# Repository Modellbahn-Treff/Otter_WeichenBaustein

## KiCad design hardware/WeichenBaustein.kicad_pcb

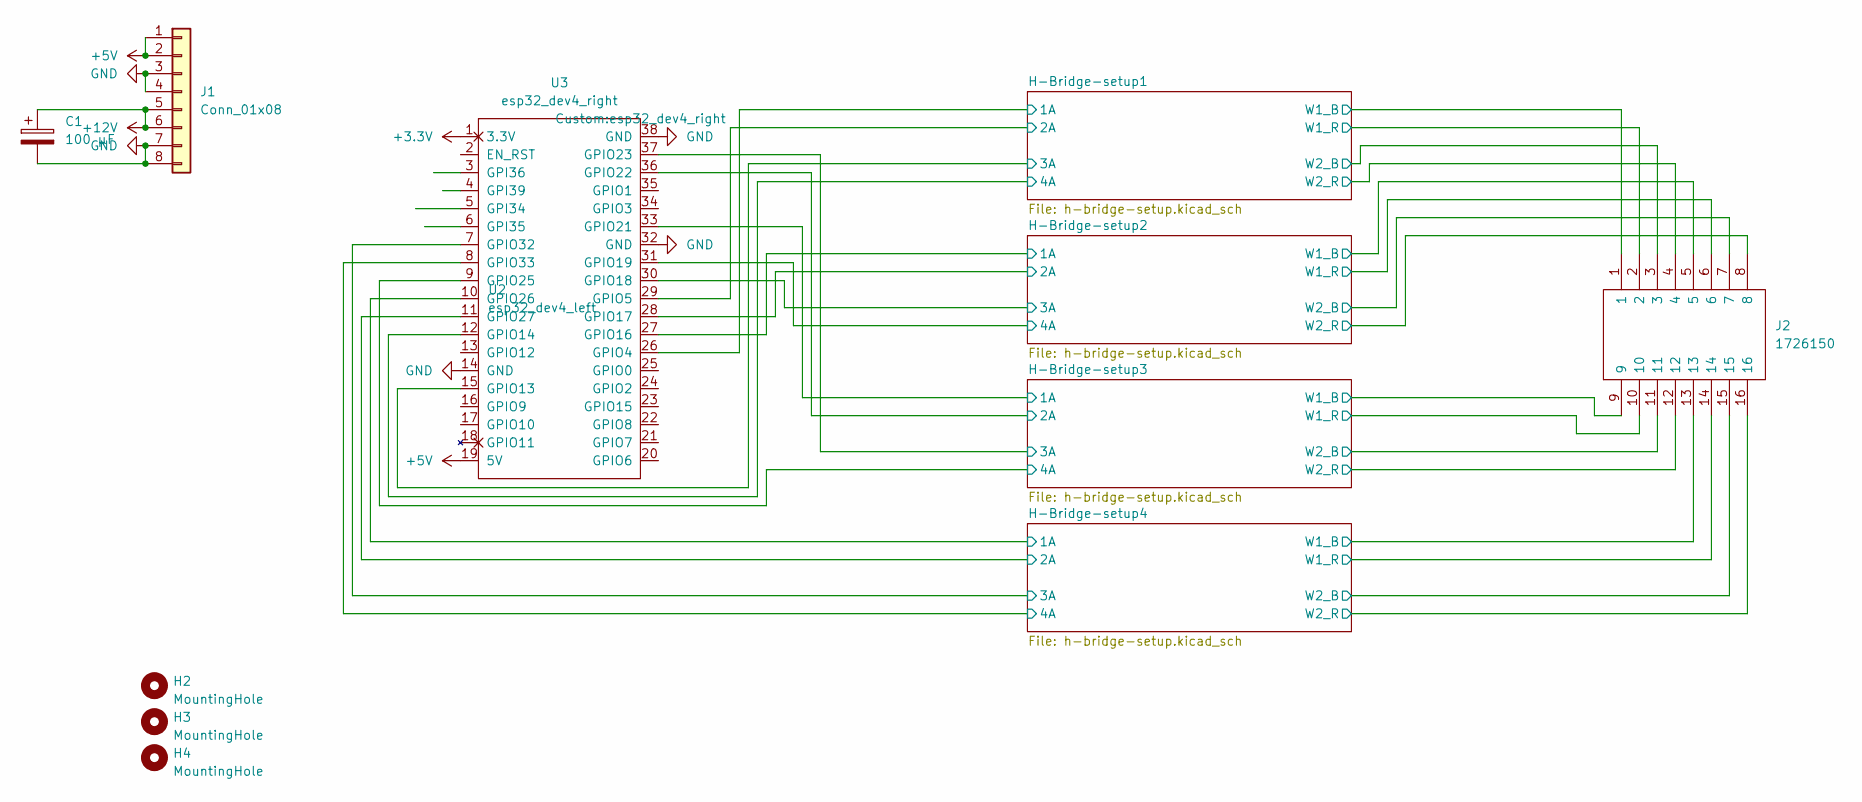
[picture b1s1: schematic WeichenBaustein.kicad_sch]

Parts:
C1: 100 µF; CP_Radial_D6.3mm_P2.50mm
H2, H3, H4: MountingHole; MountingHole_4.3mm_M4
J1: Conn_01x08; 1729186
J2: 1726150; Manufacturer_Part_Number 1726150; Mouser Part Number 651-1726150
U2: esp32_dev4_left; esp32_dev_left
U3: esp32_dev4_right

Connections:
+3.3V: U2.1 (3.3V)
+5V: J1.1, J1.2, U2.19 (5V); also elsewhere on the board
+12V: C1.1, J1.5, J1.6; also elsewhere on the board
/H-Bridge-setup1/1A: U3.26 (GPIO4); also elsewhere on the board
/H-Bridge-setup1/2A: U3.29 (GPIO5); also elsewhere on the board
/H-Bridge-setup1/3A: U2.15 (GPIO13); also elsewhere on the board
/H-Bridge-setup1/4A: U2.12 (GPIO14); also elsewhere on the board
/H-Bridge-setup1/W1_B: J2.1; also elsewhere on the board
/H-Bridge-setup1/W1_R: J2.2; also elsewhere on the board
/H-Bridge-setup1/W2_B: J2.3; also elsewhere on the board
/H-Bridge-setup1/W2_R: J2.4; also elsewhere on the board
/H-Bridge-setup2/1A: U3.27 (GPIO16); also elsewhere on the board
/H-Bridge-setup2/2A: U3.28 (GPIO17); also elsewhere on the board
/H-Bridge-setup2/3A: U3.30 (GPIO18); also elsewhere on the board
/H-Bridge-setup2/4A: U3.31 (GPIO19); also elsewhere on the board
/H-Bridge-setup2/W1_B: J2.5; also elsewhere on the board
/H-Bridge-setup2/W1_R: J2.6; also elsewhere on the board
/H-Bridge-setup2/W2_B: J2.7; also elsewhere on the board
/H-Bridge-setup2/W2_R: J2.8; also elsewhere on the board
/H-Bridge-setup3/1A: U3.33 (GPIO21); also elsewhere on the board
/H-Bridge-setup3/2A: U3.36 (GPIO22); also elsewhere on the board
/H-Bridge-setup3/3A: U3.37 (GPIO23); also elsewhere on the board
/H-Bridge-setup3/4A: U2.9 (GPIO25); also elsewhere on the board
/H-Bridge-setup3/W1_B: J2.9; also elsewhere on the board
/H-Bridge-setup3/W1_R: J2.10; also elsewhere on the board
/H-Bridge-setup3/W2_B: J2.11; also elsewhere on the board
/H-Bridge-setup3/W2_R: J2.12; also elsewhere on the board
/H-Bridge-setup4/1A: U2.10 (GPIO26); also elsewhere on the board
/H-Bridge-setup4/2A: U2.11 (GPIO27); also elsewhere on the board
/H-Bridge-setup4/3A: U2.7 (GPIO32); also elsewhere on the board
/H-Bridge-setup4/4A: U2.8 (GPIO33); also elsewhere on the board
/H-Bridge-setup4/W1_B: J2.13; also elsewhere on the board
/H-Bridge-setup4/W1_R: J2.14; also elsewhere on the board
/H-Bridge-setup4/W2_B: J2.15; also elsewhere on the board
/H-Bridge-setup4/W2_R: J2.16; also elsewhere on the board
GND: C1.2, J1.3, J1.4, J1.7, J1.8, U2.14 (GND), U3.32 (GND), U3.38 (GND); also elsewhere on the board

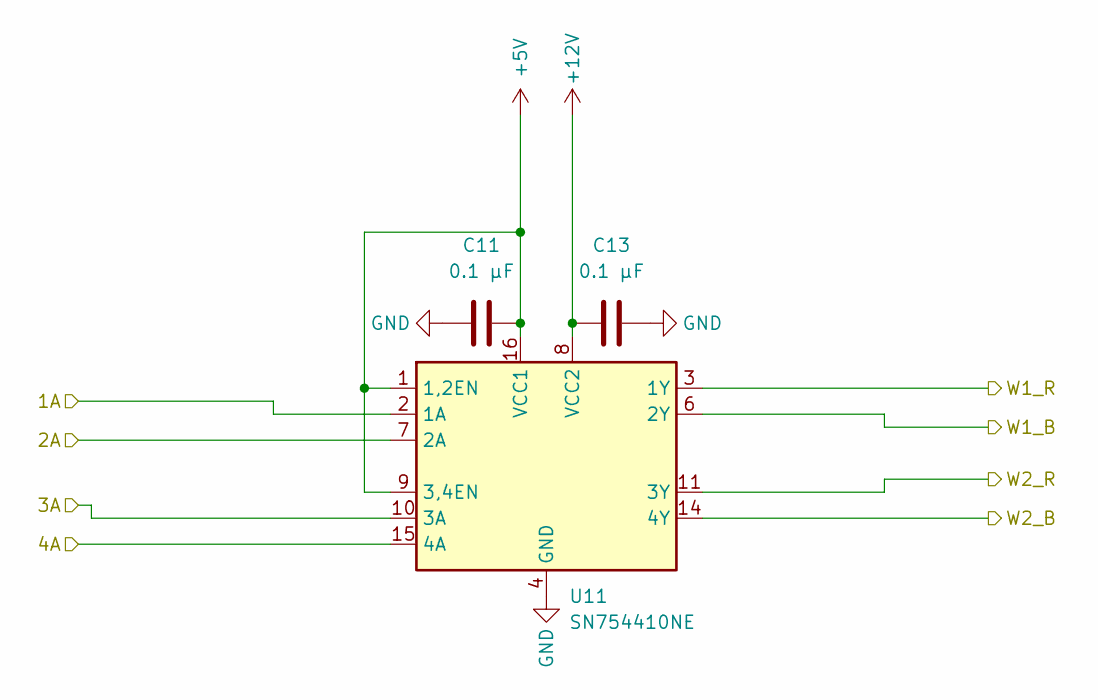
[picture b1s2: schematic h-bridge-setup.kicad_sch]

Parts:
C11, C13: 0.1 µF; C_0805_2012Metric_Pad1.18x1.45mm_HandSolder
U11: SN754410NE; DIP-16_W7.62mm

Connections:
+5V: C11.1, U11.1 (1,2EN), U11.9 (3,4EN), U11.16 (VCC1); also elsewhere on the board
+12V: C13.2, U11.8 (VCC2); also elsewhere on the board
/H-Bridge-setup1/1A: U11.2 (1A); also elsewhere on the board
/H-Bridge-setup1/2A: U11.7 (2A); also elsewhere on the board
/H-Bridge-setup1/3A: U11.10 (3A); also elsewhere on the board
/H-Bridge-setup1/4A: U11.15 (4A); also elsewhere on the board
/H-Bridge-setup1/W1_B: U11.6 (2Y); also elsewhere on the board
/H-Bridge-setup1/W1_R: U11.3 (1Y); also elsewhere on the board
/H-Bridge-setup1/W2_B: U11.14 (4Y); also elsewhere on the board
/H-Bridge-setup1/W2_R: U11.11 (3Y); also elsewhere on the board
GND: C11.2, C13.1, U11.4 (GND), U11.5 (GND), U11.12 (GND), U11.13 (GND); also elsewhere on the board

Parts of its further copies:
C21, C23, C31, C33, C41, C43: 0.1 µF; C_0805_2012Metric_Pad1.18x1.45mm_HandSolder
U21, U31, U41: SN754410NE; DIP-16_W7.62mm

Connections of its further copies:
+5V: C21.1, C31.1, C41.1, U21.1 (1,2EN), U21.9 (3,4EN), U21.16 (VCC1), U31.1 (1,2EN), U31.9 (3,4EN), U31.16 (VCC1), U41.1 (1,2EN), U41.9 (3,4EN), U41.16 (VCC1); also elsewhere on the board
+12V: C23.2, C33.2, C43.2, U21.8 (VCC2), U31.8 (VCC2), U41.8 (VCC2); also elsewhere on the board
/H-Bridge-setup2/1A: U21.2 (1A); also elsewhere on the board
/H-Bridge-setup2/2A: U21.7 (2A); also elsewhere on the board
/H-Bridge-setup2/3A: U21.10 (3A); also elsewhere on the board
/H-Bridge-setup2/4A: U21.15 (4A); also elsewhere on the board
/H-Bridge-setup2/W1_B: U21.6 (2Y); also elsewhere on the board
/H-Bridge-setup2/W1_R: U21.3 (1Y); also elsewhere on the board
/H-Bridge-setup2/W2_B: U21.14 (4Y); also elsewhere on the board
/H-Bridge-setup2/W2_R: U21.11 (3Y); also elsewhere on the board
/H-Bridge-setup3/1A: U31.2 (1A); also elsewhere on the board
/H-Bridge-setup3/2A: U31.7 (2A); also elsewhere on the board
/H-Bridge-setup3/3A: U31.10 (3A); also elsewhere on the board
/H-Bridge-setup3/4A: U31.15 (4A); also elsewhere on the board
/H-Bridge-setup3/W1_B: U31.6 (2Y); also elsewhere on the board
/H-Bridge-setup3/W1_R: U31.3 (1Y); also elsewhere on the board
/H-Bridge-setup3/W2_B: U31.14 (4Y); also elsewhere on the board
/H-Bridge-setup3/W2_R: U31.11 (3Y); also elsewhere on the board
/H-Bridge-setup4/1A: U41.2 (1A); also elsewhere on the board
/H-Bridge-setup4/2A: U41.7 (2A); also elsewhere on the board
/H-Bridge-setup4/3A: U41.10 (3A); also elsewhere on the board
/H-Bridge-setup4/4A: U41.15 (4A); also elsewhere on the board
/H-Bridge-setup4/W1_B: U41.6 (2Y); also elsewhere on the board
/H-Bridge-setup4/W1_R: U41.3 (1Y); also elsewhere on the board
/H-Bridge-setup4/W2_B: U41.14 (4Y); also elsewhere on the board
/H-Bridge-setup4/W2_R: U41.11 (3Y); also elsewhere on the board
GND: C21.2, C23.1, C31.2, C33.1, C41.2, C43.1, U21.4 (GND), U21.5 (GND), U21.12 (GND), U21.13 (GND), U31.4 (GND), U31.5 (GND), U31.12 (GND), U31.13 (GND), U41.4 (GND), U41.5 (GND), U41.12 (GND), U41.13 (GND); also elsewhere on the board

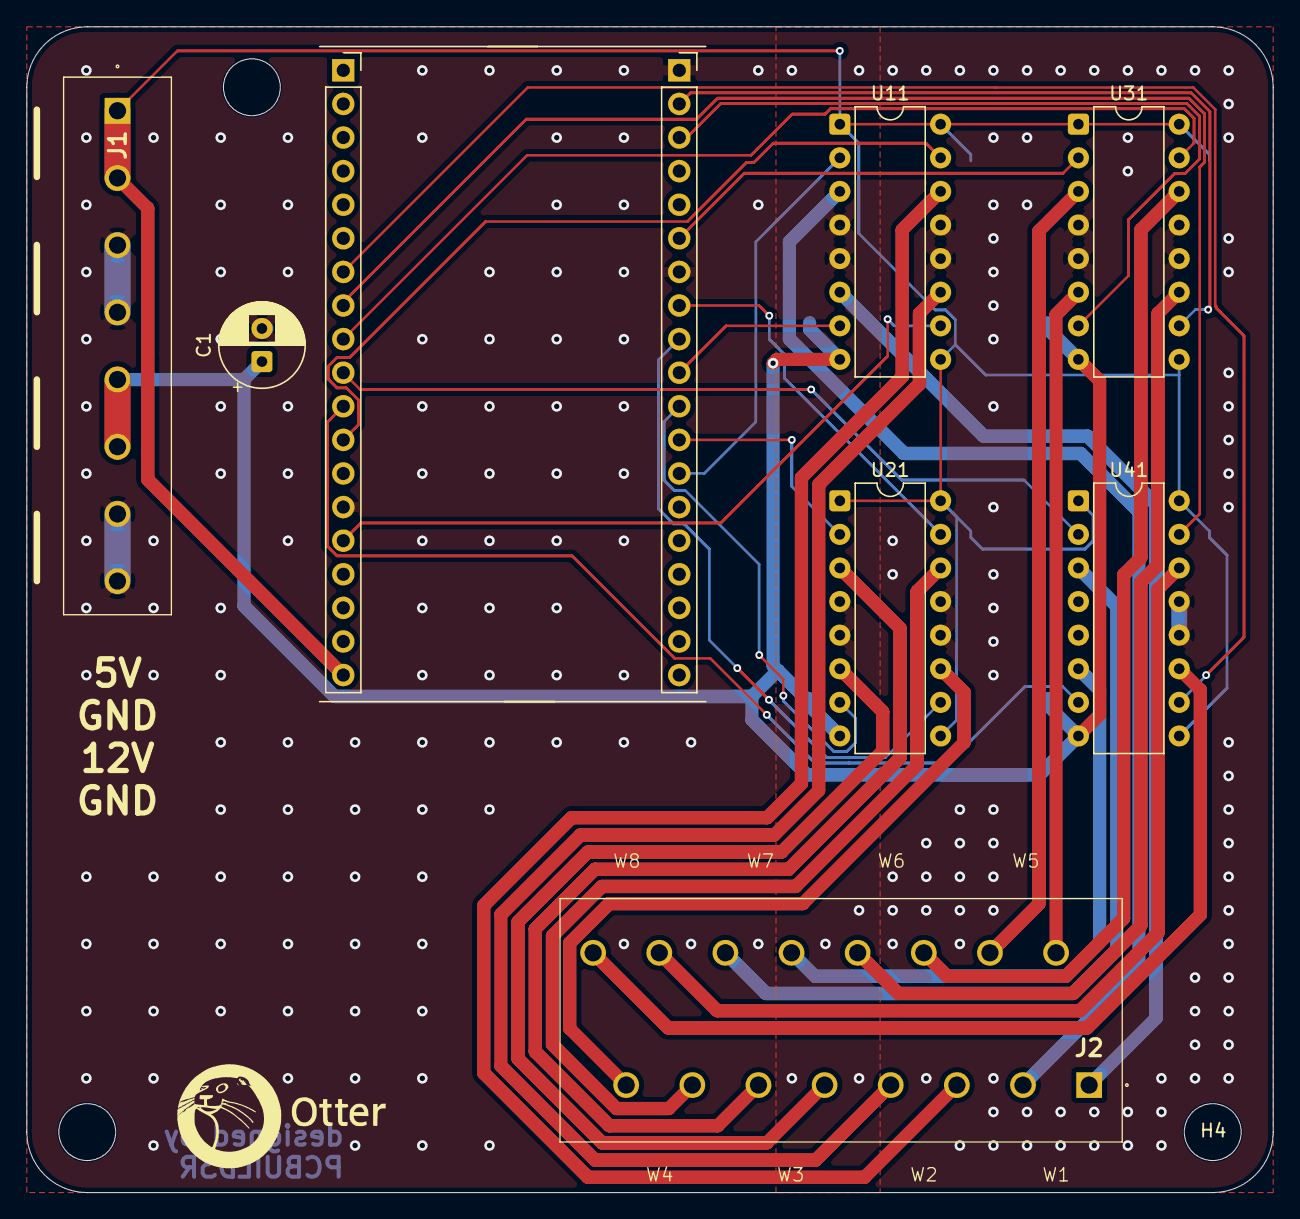
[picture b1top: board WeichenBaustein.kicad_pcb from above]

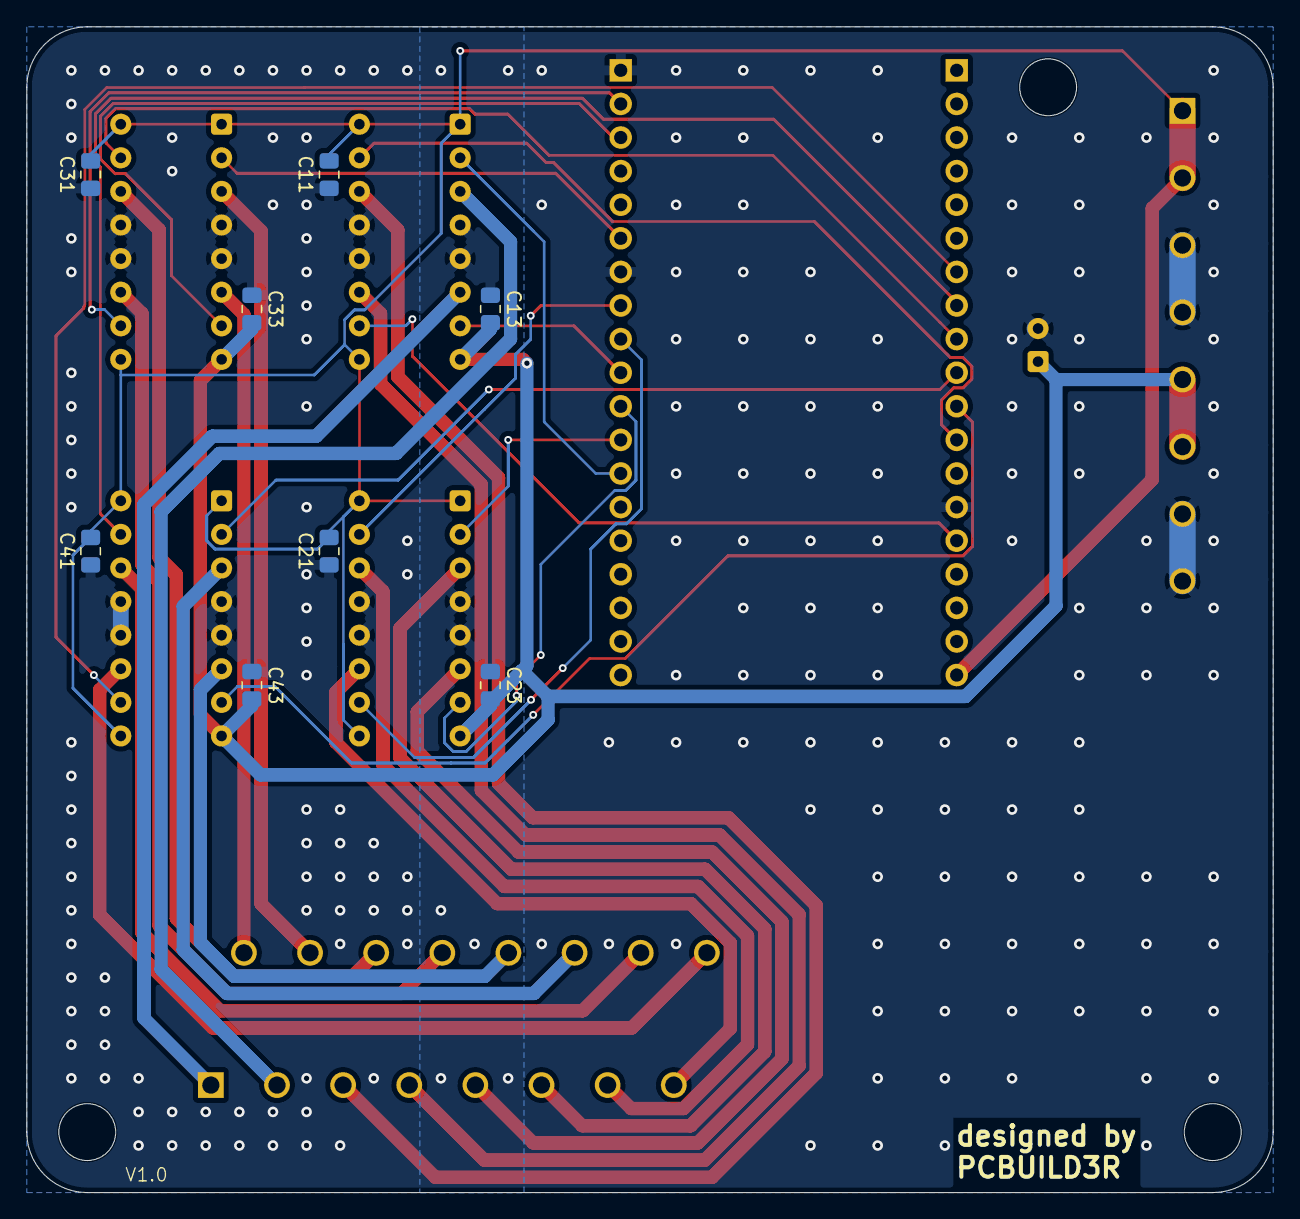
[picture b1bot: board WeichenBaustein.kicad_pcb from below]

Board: 2 copper layers, 94.2 x 88.1 mm, 20 parts (8 on the bottom side), 35 nets.

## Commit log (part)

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2026-04-12 Add .DS_Store to .gitignore
2026-04-17 scematics and basic PCB layout
2026-05-02 basic routing
2026-05-02 final design
2026-05-03 add version number
2026-06-16 add ibom
